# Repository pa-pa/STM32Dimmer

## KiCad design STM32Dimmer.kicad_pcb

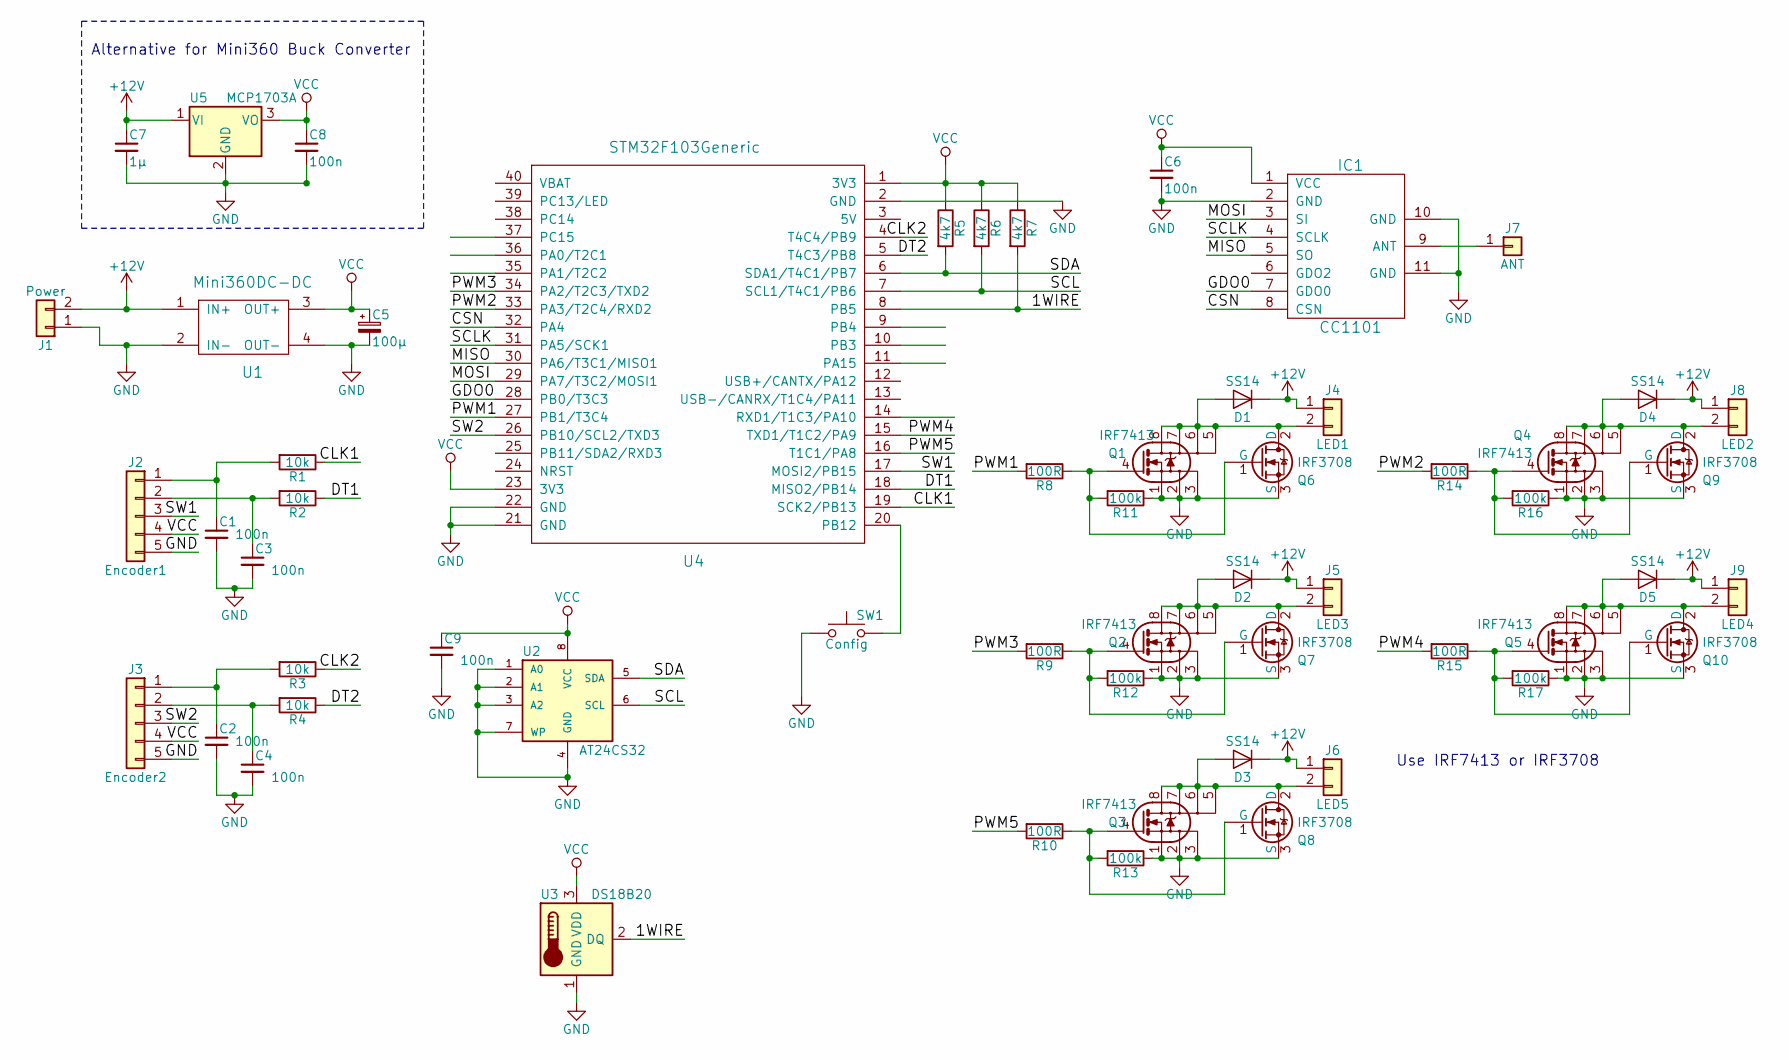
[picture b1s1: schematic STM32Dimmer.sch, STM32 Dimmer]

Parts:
C1, C2, C3, C4, C6, C8, C9: 100n; C_0805
C5: 100µ; RADIAL_2.5mm_6.3mm
C7: 1µ; C_0805
D1, D2, D3, D4, D5: SS14; D_SMA
IC1: CC1101; CC1101_Module
J1: Power; TerminalBlock_bornier-2_P5.08mm
J2: Encoder1; Pin_Header_Straight_1x05_Pitch2.54mm
J3: Encoder2; Pin_Header_Straight_1x05_Pitch2.54mm
J4: LED1; TerminalBlock_bornier-2_P5.08mm
J5: LED3; TerminalBlock_bornier-2_P5.08mm
J6: LED5; TerminalBlock_bornier-2_P5.08mm
J7: ANT; Pin_Header_Straight_1x01_Pitch2.54mm
J8: LED2; TerminalBlock_bornier-2_P5.08mm
J9: LED4; TerminalBlock_bornier-2_P5.08mm
Q1, Q2, Q3, Q4, Q5: IRF7413; SOIC-8_3.9x4.9mm_Pitch1.27mm
Q6, Q7, Q8, Q9, Q10: IRF3708; TO-220-3_Vertical
R1, R2, R3, R4: 10k; R_0805
R5, R6, R7: 4k7; R_0805
R8, R9, R10, R14, R15: 100R; R_0805
R11, R12, R13, R16, R17: 100k; R_0805
SW1: Config; SW_SPST_B3U-1000P
U1: Mini360DC-DC; Mini360D_SM
U2: AT24CS32; SOIC-8_3.9x4.9mm_Pitch1.27mm
U3: DS18B20; TO-92_Inline_Narrow_Oval
U4: STM32F103Generic
U5: MCP1703A; SOT-223-3_TabPin2

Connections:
+12V: C7.1, D1.1 (K), D2.1 (K), D3.1 (K), D4.1 (K), D5.1 (K), J1.2, J4.1, J5.1, J6.1, J8.1, J9.1, U1.1 (IN+), U5.1 (VI)
/1WIRE: R7.2, U3.2 (DQ), U4.8 (PB5)
/CLK1: R1.1, U4.19 (SCK2/PB13)
/CLK2: R3.1, U4.4 (T4C4/PB9)
/CSN: IC1.8 (CSN), U4.32 (PA4)
/DT1: R2.1, U4.18 (MISO2/PB14)
/DT2: R4.1, U4.5 (T4C3/PB8)
/GDO0: IC1.7 (GDO0), U4.28 (PB0/T3C3)
/MISO: IC1.5 (SO), U4.30 (PA6/T3C1/MISO1)
/MOSI: IC1.3 (SI), U4.29 (PA7/T3C2/MOSI1)
/PWM1: R8.2, U4.27 (PB1/T3C4)
/PWM2: R14.2, U4.33 (PA3/T2C4/RXD2)
/PWM3: R9.2, U4.34 (PA2/T2C3/TXD2)
/PWM4: R15.2, U4.15 (TXD1/T1C2/PA9)
/PWM5: R10.2, U4.16 (T1C1/PA8)
/SCL: R6.2, U2.6 (SCL), U4.7 (SCL1/T4C1/PB6)
/SCLK: IC1.4 (SCLK), U4.31 (PA5/SCK1)
/SDA: R5.2, U2.5 (SDA), U4.6 (SDA1/T4C1/PB7)
/SW1: J2.3, U4.17 (MOSI2/PB15)
/SW2: J3.3, U4.26 (PB10/SCL2/TXD3)
GND: C1.2, C2.2, C3.2, C4.2, C5.2, C6.2, C7.2, C8.2, C9.2, IC1.2 (GND), IC1.10 (GND), IC1.11 (GND), J1.1, J2.5, J3.5, Q1.1 (S), Q1.2, Q1.3, Q2.1 (S), Q2.2, Q2.3, Q3.1 (S), Q3.2, Q3.3, Q4.1 (S), Q4.2, Q4.3, Q5.1 (S), Q5.2, Q5.3, Q6.3 (S), Q7.3 (S), Q8.3 (S), Q9.3 (S), Q10.3 (S), R11.1, R12.1, R13.1, R16.1, R17.1, SW1.1, U1.2 (IN-), U1.4 (OUT-), U2.1 (A0), U2.2 (A1), U2.3 (A2), U2.4 (GND), U2.7 (WP), U3.1 (GND), U4.2 (GND), U4.21 (GND), U4.22 (GND), U5.2 (GND)
unnamed: C1.1, J2.1, R1.2
unnamed: C2.1, J3.1, R3.2
unnamed: C3.1, J2.2, R2.2
unnamed: C4.1, J3.2, R4.2
unnamed: D1.2 (A), J4.2, Q1.5, Q1.6, Q1.7, Q1.8 (D), Q6.2 (D)
unnamed: D2.2 (A), J5.2, Q2.5, Q2.6, Q2.7, Q2.8 (D), Q7.2 (D)
unnamed: D3.2 (A), J6.2, Q3.5, Q3.6, Q3.7, Q3.8 (D), Q8.2 (D)
unnamed: D4.2 (A), J8.2, Q4.5, Q4.6, Q4.7, Q4.8 (D), Q9.2 (D)
unnamed: D5.2 (A), J9.2, Q5.5, Q5.6, Q5.7, Q5.8 (D), Q10.2 (D)
unnamed: IC1.9 (ANT), J7.1
unnamed: Q1.4 (G), Q6.1 (G), R8.1, R11.2
unnamed: Q2.4 (G), Q7.1 (G), R9.1, R12.2
unnamed: Q3.4 (G), Q8.1 (G), R10.1, R13.2
unnamed: Q4.4 (G), Q9.1 (G), R14.1, R16.2
unnamed: Q5.4 (G), Q10.1 (G), R15.1, R17.2
unnamed: SW1.2, U4.20 (PB12)
VCC: C5.1, C6.1, C8.1, C9.1, IC1.1 (VCC), J2.4, J3.4, R5.1, R6.1, R7.1, U1.3 (OUT+), U2.8 (VCC), U3.3 (VDD), U4.1 (3V3), U4.23 (3V3), U5.3 (VO)

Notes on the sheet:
Alternative for Mini360 Buck Converter
Use IRF7413 or IRF3708

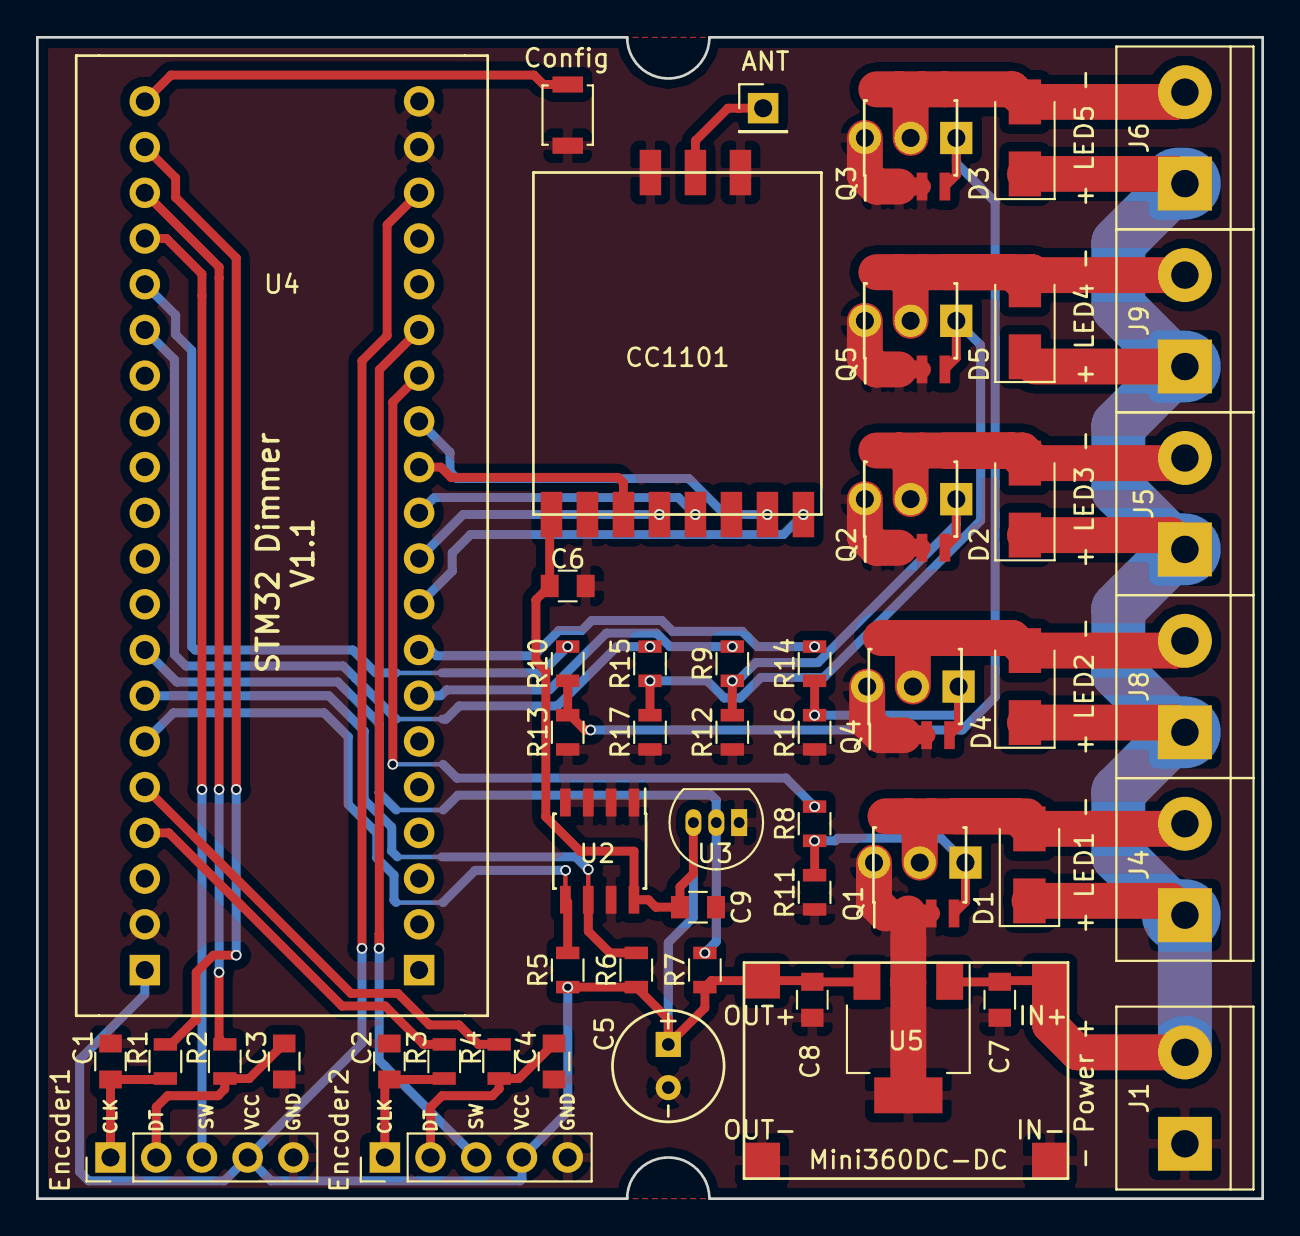
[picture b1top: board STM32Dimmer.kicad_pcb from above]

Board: 2 copper layers, 68.1 x 64.5 mm, 57 parts (0 on the bottom side), 38 nets.

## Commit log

2018-08-10 checkin
2018-08-29 v1.1
2018-08-30 small updates / gerber added
2018-09-13 case added
2021-09-27 add stl files
